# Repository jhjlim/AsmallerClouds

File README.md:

# AsmallerClouds
Schematic/board files for an 8HP version of Clouds

This Eagle project uses the original mutable instruments design files. It simply repositions all components to fit in an 8HP module.
I did this layout as a side project because I love the clouds module and wanted more in my system without sacrificing other space! The only component changes are the crystals to a smaller package, 3mm red/green LEDs and a different illuminated push button. The RESET(SW5) and SYSBOOT(SW4) tactile switches were also dropped and replaced with accesible pads that can be shorted.

Original CAD file, PCB & Schematic and original design elements provided by Mutable Instruments under creative commons CC-BY-SA-3.0 license.

Design contributions are provided by Jason H. J. Lim under Creative Commons CC-BY-SA-3.0 license.

Support of DIY builds is not provided by myself nor Mutable Instruments nor the Mutable Instruments forums, please respect their wishes to not want to answer any questions regarding DIY builds and leave them to continue doing what they do best.

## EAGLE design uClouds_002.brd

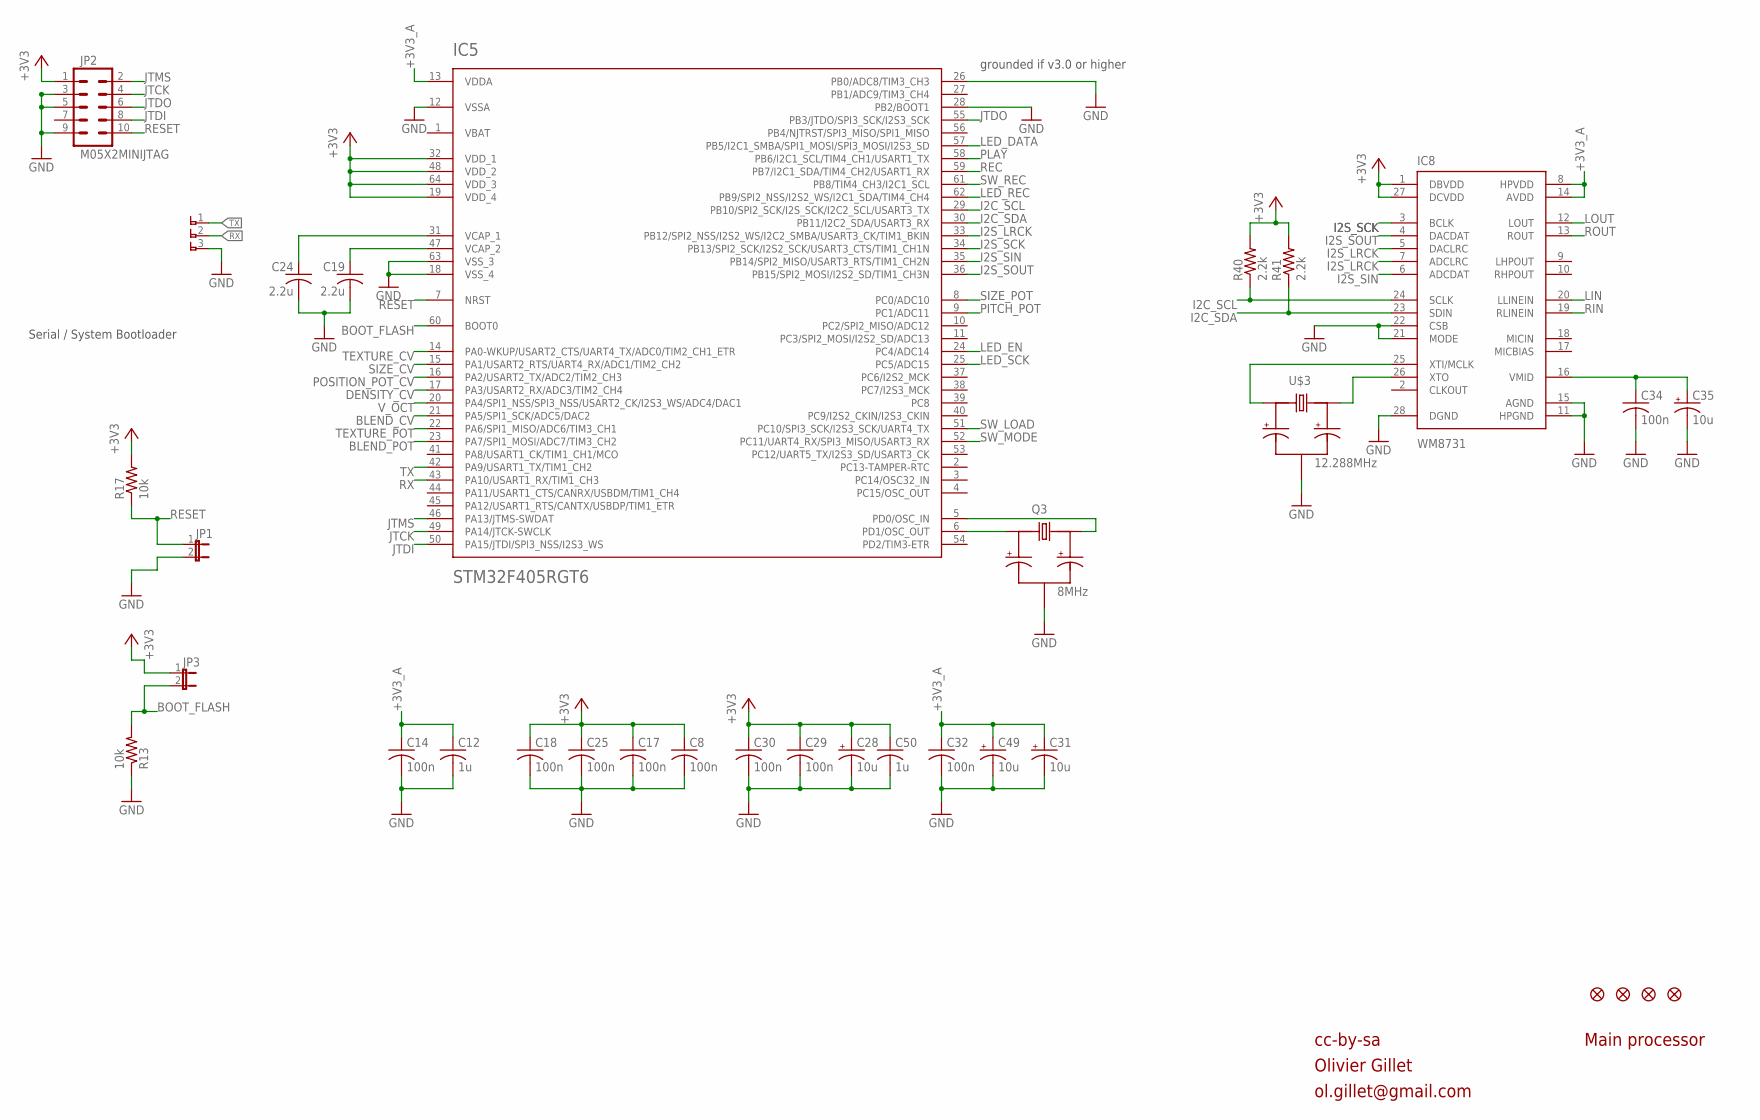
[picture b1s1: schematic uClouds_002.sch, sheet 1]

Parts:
C8, C32, C34: 100n; C0603
C12, C50: 1u; C0603K
C14, C17, C18, C25, C29, C30: 100n; C0603K
C19, C24: 2.2u; C0805K
C28: 10u; 153CLV-0405
C31, C35: 10u; PANASONIC_B
C49: 10u; PANASONIC_A
F1, F2, F3, F4: FIDUCIAL1X2; FIDUCIAL-1X2
IC5: STM32F405RGT6; TQFP-10X10-64
IC8: WM8731; SSOP28
JP1, JP3: JUMPER-2SMD-NO; SJ_2S-NO
JP2: M05X2MINIJTAG; 2X5-1.27
Q3: 8MHz; CRYSTAL_SMALLER
R13, R17: 10k; R0603
R40, R41: 2.2k; R0603
U$3: 12.288MHz; CRYSTAL_SMALLER
U$4: 1X3_SMALL

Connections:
+3V3: C8.1, C17.1, C18.1, C25.1, C28.+, C29.1, C30.1, C50.1, IC5.19 (VDD_4), IC5.32 (VDD_1), IC5.48 (VDD_2), IC5.64 (VDD_3), IC8.1 (DBVDD), IC8.27 (DCVDD), JP2.1, JP3.1, R17.2, R40.2, R41.2; also elsewhere on the board
+3V3_A: C12.1, C14.1, C31.+, C32.1, C49.+, IC5.13 (VDDA), IC8.8 (HPVDD), IC8.14 (AVDD); also elsewhere on the board
BLEND_CV: IC5.21 (PA5/SPI1_SCK/ADC5/DAC2); also elsewhere on the board
BLEND_POT: IC5.23 (PA7/SPI1_MOSI/ADC7/TIM3_CH2); also elsewhere on the board
BOOT_FLASH: IC5.60 (BOOT0), JP3.2, R13.2
DENSITY_CV: IC5.17 (PA3/USART2_RX/ADC3/TIM2_CH4); also elsewhere on the board
GND: C8.2, C12.2, C14.2, C17.2, C18.2, C19.2, C24.2, C25.2, C28.-, C29.2, C30.2, C31.-, C32.2, C34.2, C35.-, C49.-, C50.2, IC5.12 (VSSA), IC5.18 (VSS_4), IC5.26 (PB0/ADC8/TIM3_CH3), IC5.28 (PB2/BOOT1), IC5.63 (VSS_3), IC8.11 (HPGND), IC8.15 (AGND), IC8.21 (MODE), IC8.22 (CSB), IC8.28 (DGND), JP1.2, JP2.3, JP2.5, JP2.9, Q3.GND, R13.1, U$3.GND, U$4.3; also elsewhere on the board
I2C_SCL: IC5.29 (PB10/SPI2_SCK/I2S_SCK/I2C2_SCL/USART3_TX), IC8.24 (SCLK), R40.1
I2C_SDA: IC5.30 (PB11/I2C2_SDA/USART3_RX), IC8.23 (SDIN), R41.1
I2S_LRCK: IC5.33 (PB12/SPI2_NSS/I2S2_WS/I2C2_SMBA/USART3_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), IC8.5 (DACLRC), IC8.7 (ADCLRC)
I2S_SCK: IC5.34 (PB13/SPI2_SCK/I2S2_SCK/USART3_CTS/TIM1_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), IC8.3 (BCLK)
I2S_SIN: IC5.35 (PB14/SPI2_MISO/USART3_RTS/TIM1_CH2N), IC8.6 (ADCDAT)
I2S_SOUT: IC5.36 (PB15/SPI2_MOSI/I2S2_SD/TIM1_CH3N), IC8.4 (DACDAT)
JTCK: IC5.49 (PA14/JTCK-SWCLK), JP2.4
JTDI: IC5.50 (PA15/JTDI/SPI3_NSS/I2S3_WS), JP2.8
JTDO: IC5.55 (PB3/JTDO/SPI3_SCK/I2S3_SCK), JP2.6
JTMS: IC5.46 (PA13/JTMS-SWDAT), JP2.2
LED_DATA: IC5.57 (PB5/I2C1_SMBA/SPI1_MOSI/SPI3_MOSI/I2S3_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); also elsewhere on the board
LED_EN: IC5.24 (PC4/ADC14); also elsewhere on the board
LED_REC: IC5.62 (PB9/SPI2_NSS/I2S2_WS/I2C1_SDA/TIM4_CH4); also elsewhere on the board
LED_SCK: IC5.25 (PC5/ADC15); also elsewhere on the board
LIN: IC8.20 (LLINEIN); also elsewhere on the board
LOUT: IC8.12 (LOUT); also elsewhere on the board
unnamed: IC5.6 (PD1/OSC_OUT), Q3.X1
unnamed: IC8.25 (XTI/MCLK), U$3.X1
unnamed: IC5.5 (PD0/OSC_IN), Q3.X2
unnamed: C19.1, IC5.47 (VCAP_2)
unnamed: C34.1, C35.+, IC8.16 (VMID)
unnamed: C24.1, IC5.31 (VCAP_1)
unnamed: IC8.26 (XTO), U$3.X2
PITCH_POT: IC5.9 (PC1/ADC11); also elsewhere on the board
PLAY: IC5.58 (PB6/I2C1_SCL/TIM4_CH1/USART1_TX); also elsewhere on the board
POSITION_POT_CV: IC5.16 (PA2/USART2_TX/ADC2/TIM2_CH3); also elsewhere on the board
REC: IC5.59 (PB7/I2C1_SDA/TIM4_CH2/USART1_RX); also elsewhere on the board
RESET: IC5.7 (NRST), JP1.1, JP2.10, R17.1
RIN: IC8.19 (RLINEIN); also elsewhere on the board
ROUT: IC8.13 (ROUT); also elsewhere on the board
RX: IC5.43 (PA10/USART1_RX/TIM1_CH3), U$4.2
SIZE_CV: IC5.15 (PA1/USART2_RTS/UART4_RX/ADC1/TIM2_CH2); also elsewhere on the board
SIZE_POT: IC5.8 (PC0/ADC10); also elsewhere on the board
SW_LOAD: IC5.51 (PC10/SPI3_SCK/I2S3_SCK/UART4_TX); also elsewhere on the board
SW_MODE: IC5.52 (PC11/UART4_RX/SPI3_MISO/USART3_RX); also elsewhere on the board
SW_REC: IC5.61 (PB8/TIM4_CH3/I2C1_SCL); also elsewhere on the board
TEXTURE_CV: IC5.14 (PA0-WKUP/USART2_CTS/UART4_TX/ADC0/TIM2_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); also elsewhere on the board
TEXTURE_POT: IC5.22 (PA6/SPI1_MISO/ADC6/TIM3_CH1); also elsewhere on the board
TX: IC5.42 (PA9/USART1_TX/TIM1_CH2), U$4.1
VBAT: IC5.1 (VBAT)
V_OCT: IC5.20 (PA4/SPI1_NSS/SPI3_NSS/USART2_CK/I2S3_WS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); also elsewhere on the board

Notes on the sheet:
cc-by-sa
Olivier Gillet
ol.gillet@gmail.com
Main processor
Serial / System Bootloader
grounded if v3.0 or higher

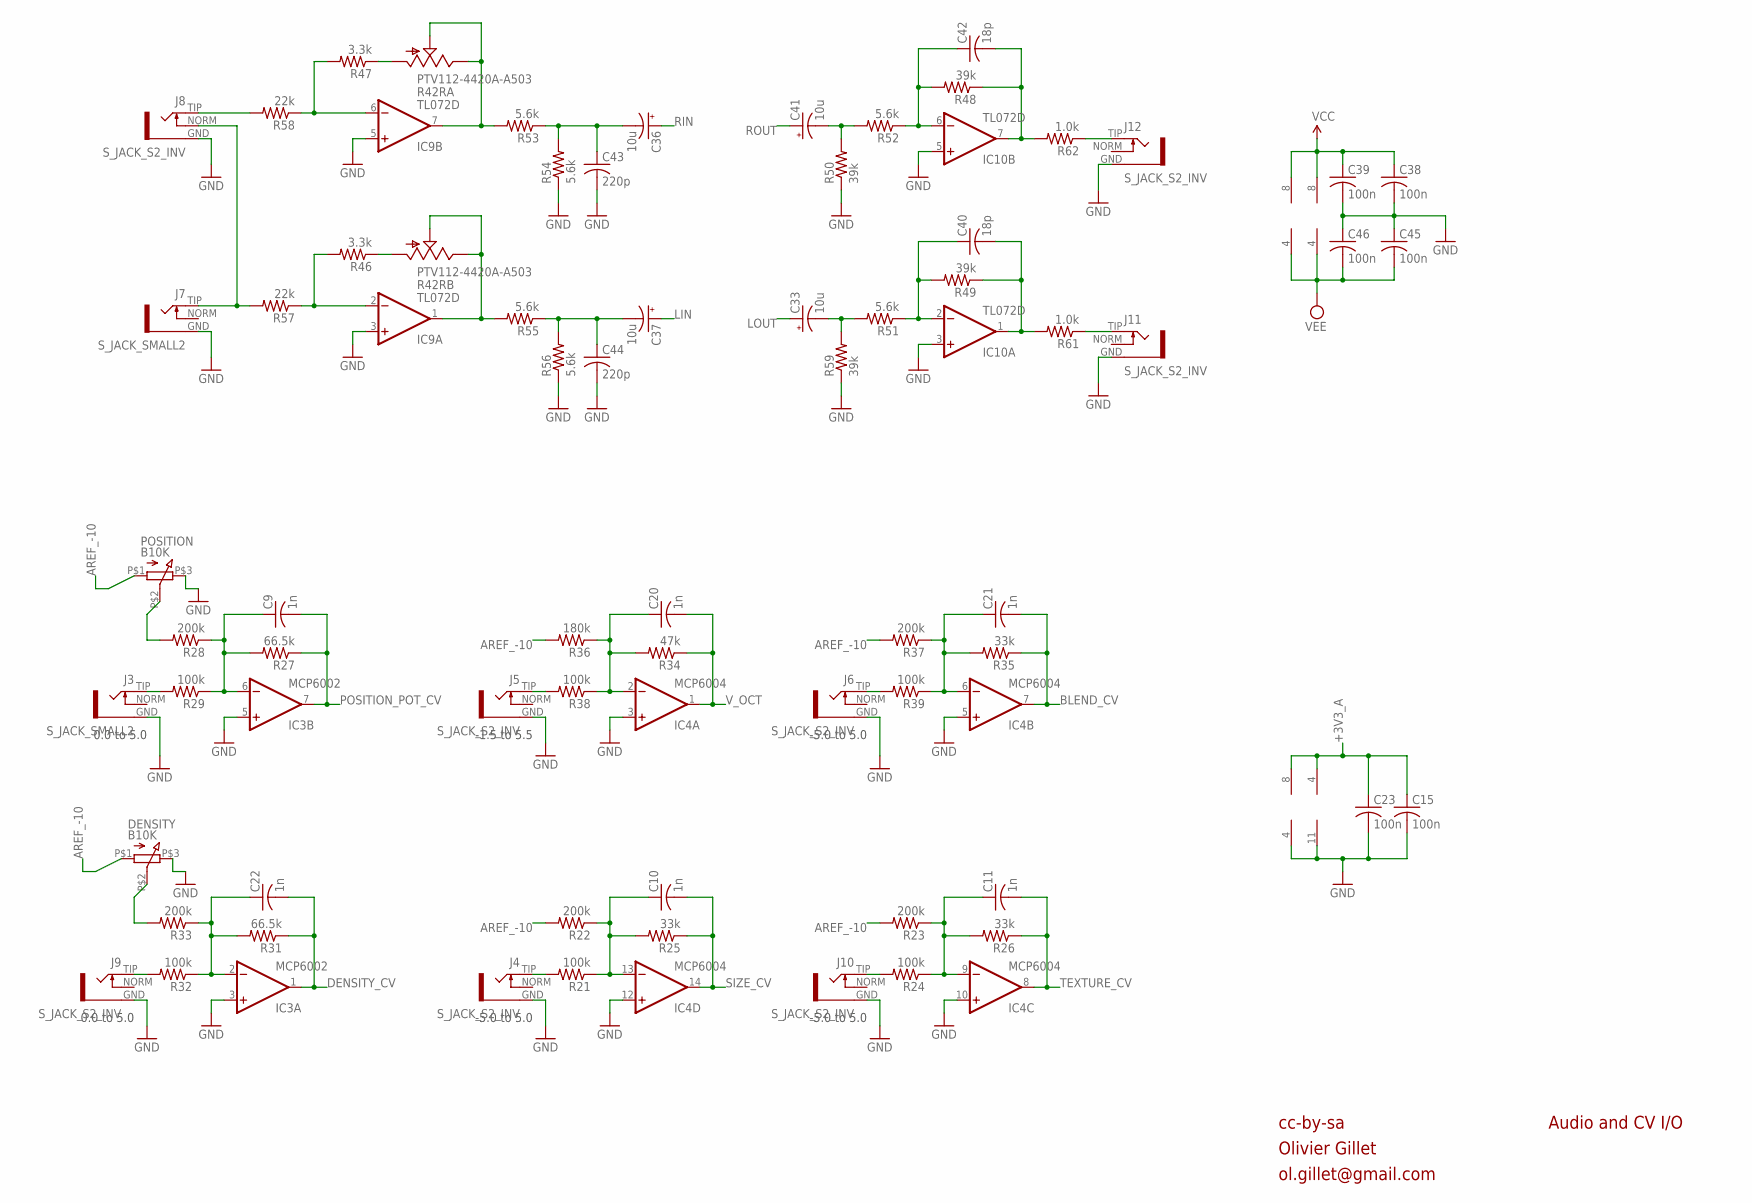
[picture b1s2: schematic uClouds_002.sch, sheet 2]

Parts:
C9, C10, C11, C20, C21, C22: 1n; C0603
C15, C39, C46: 100n; C0603K
C23, C38, C45: 100n; C0603
C33, C36, C37, C41: 10u; PANASONIC_B
C40, C42: 18p; C0603
C43: 220p; C0603K
C44: 220p; C0603
DENSITY: B10K; Q-POT2
IC3: MCP6002; SO08
IC4: MCP6004; SO14
IC9, IC10: TL072D; SO08
J3, J7: S_JACK_SMALL2
J4, J5, J6, J8, J9, J10, J11, J12: S_JACK_S2_INV
POSITION: B10K; Q-POT2
R21, R24, R29, R32, R38, R39: 100k; R0603
R22, R23, R28, R33, R37: 200k; R0603
R25, R26, R35: 33k; R0603
R27, R31: 66.5k; R0603
R34: 47k; R0603
R36: 180k; R0603
R42: PTV112-4420A-A503; BOURNS_PTV112
R46, R47: 3.3k; R0603
R48, R49, R50, R59: 39k; R0603
R51, R52, R53, R54, R55, R56: 5.6k; R0603
R57, R58: 22k; R0603
R61, R62: 1.0k; R0603

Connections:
+3V3_A: C15.1, C23.1, IC3.8 (V+), IC4.4 (V+); also elsewhere on the board
AREF_-10: DENSITY.P$1 (1), POSITION.P$1 (1), R22.2, R23.2, R36.2, R37.2; also elsewhere on the board
BLEND_CV: C21.2, IC4.7 (OUT), R35.1; also elsewhere on the board
DENSITY_CV: C22.2, IC3.1 (OUT), R31.1; also elsewhere on the board
GND: C15.2, C23.2, C38.2, C39.2, C43.2, C44.2, C45.1, C46.1, DENSITY.P$3 (3), IC3.3 (+IN), IC3.4 (V-), IC3.5 (+IN), IC4.3 (+IN), IC4.5 (+IN), IC4.10 (+IN), IC4.11 (V-), IC4.12 (+IN), IC9.3 (+IN), IC9.5 (+IN), IC10.3 (+IN), IC10.5 (+IN), J3.GND, J4.GND, J5.GND, J6.GND, J7.GND, J8.GND, J9.GND, J10.GND, J11.GND, J12.GND, POSITION.P$3 (3), R50.1, R54.1, R56.1, R59.1; also elsewhere on the board
LIN: C37.+; also elsewhere on the board
LOUT: C33.+; also elsewhere on the board
LOUT_JACK: J11.TIP, R61.1
unnamed: J4.TIP, R21.2
unnamed: C10.1, IC4.13 (-IN), R21.1, R22.1, R25.2
unnamed: J10.TIP, R24.2
unnamed: C11.1, IC4.9 (-IN), R23.1, R24.1, R26.2
unnamed: J6.TIP, R39.2
unnamed: J5.TIP, R38.2
unnamed: C20.1, IC4.2 (-IN), R34.2, R36.1, R38.1
unnamed: J9.TIP, R32.2
unnamed: C21.1, IC4.6 (-IN), R35.2, R37.1, R39.1
unnamed: C37.-, C44.1, R55.1, R56.2
unnamed: J8.TIP, R58.2
unnamed: J7.TIP, J8.NORM, R57.2
unnamed: C36.-, C43.1, R53.1, R54.2
unnamed: C41.-, R50.2, R52.2
unnamed: C22.1, IC3.2 (-IN), R31.2, R32.1, R33.1
unnamed: C42.1, IC10.6 (-IN), R48.2, R52.1
unnamed: DENSITY.P$2 (2), R33.2
unnamed: J3.TIP, R29.2
unnamed: C42.2, IC10.7 (OUT), R48.1, R62.2
unnamed: C9.1, IC3.6 (-IN), R27.2, R28.1, R29.1
unnamed: C33.-, R51.2, R59.2
unnamed: C40.1, IC10.2 (-IN), R49.2, R51.1
unnamed: C40.2, IC10.1 (OUT), R49.1, R61.2
unnamed: POSITION.P$2 (2), R28.2
unnamed: IC9.7 (OUT), R42.2P (S), R42.3P (E), R53.2
unnamed: IC9.1 (OUT), R42.2 (S), R42.3 (E), R55.2
unnamed: R42.1P (A), R47.1
unnamed: R42.1 (A), R46.1
unnamed: IC9.6 (-IN), R47.2, R58.1
unnamed: IC9.2 (-IN), R46.2, R57.1
POSITION_POT_CV: C9.2, IC3.7 (OUT), R27.1; also elsewhere on the board
RIN: C36.+; also elsewhere on the board
ROUT: C41.+; also elsewhere on the board
ROUT_JACK: J12.TIP, R62.1
SIZE_CV: C10.2, IC4.14 (OUT), R25.1; also elsewhere on the board
TEXTURE_CV: C11.2, IC4.8 (OUT), R26.1; also elsewhere on the board
VCC: C38.1, C39.1, IC9.8 (V+), IC10.8 (V+); also elsewhere on the board
VEE: C45.2, C46.2, IC9.4 (V-), IC10.4 (V-); also elsewhere on the board
V_OCT: C20.2, IC4.1 (OUT), R34.1; also elsewhere on the board

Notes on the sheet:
cc-by-sa
Olivier Gillet
ol.gillet@gmail.com
Audio and CV I/O
0.0 to 5.0
-1.5 to 5.5
-5.0 to 5.0

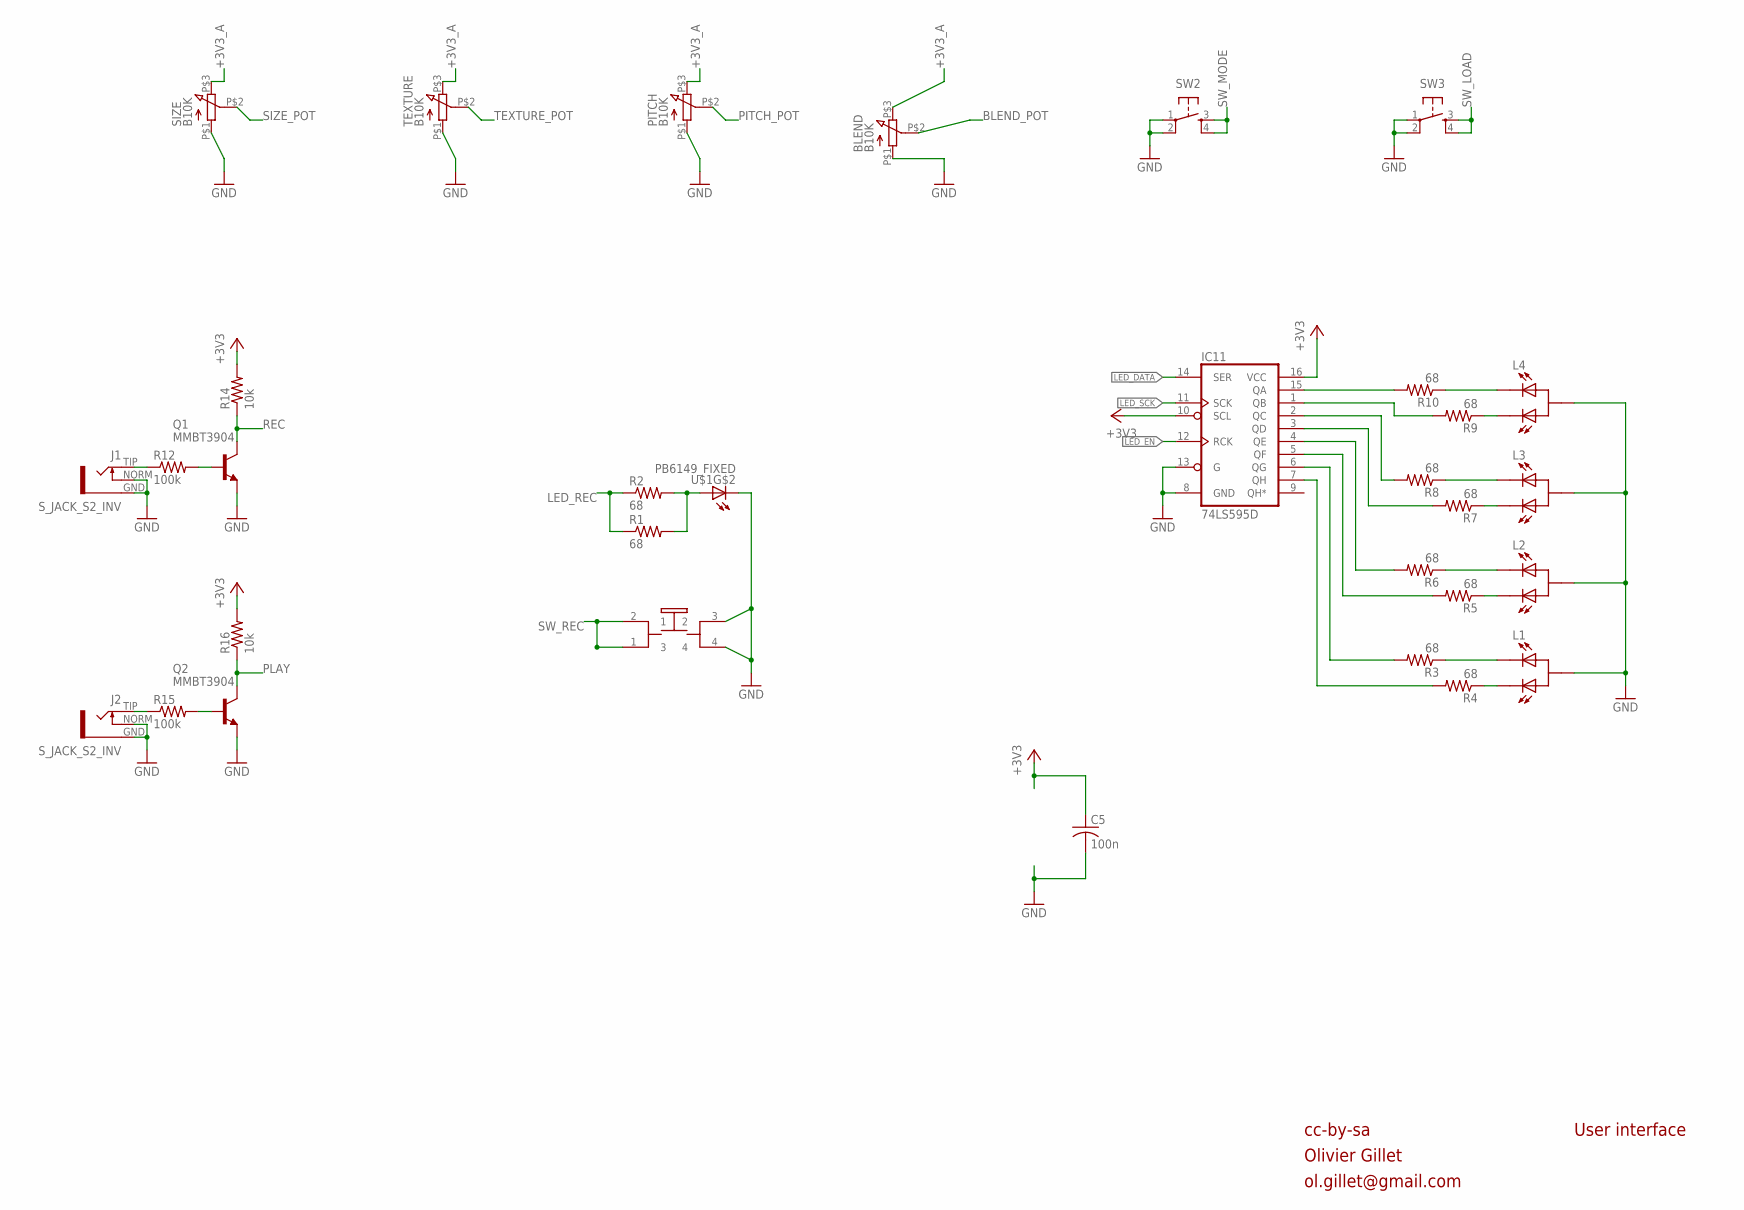
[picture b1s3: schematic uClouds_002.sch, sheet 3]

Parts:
BLEND: B10K; Q-POT2
C5: 100n; C0603
IC11: 74LS595D; SO16
J1, J2: S_JACK_S2_INV
L1, L2, L3, L4: LED_3MM_3PIN
PITCH: B10K; Q-POT2
Q1, Q2: MMBT3904; SOT23-BEC
R1, R2, R3, R4, R5, R6, R7, R8, R9, R10: 68; R0603
R12, R15: 100k; R0603
R14, R16: 10k; R0603
SIZE: B10K; Q-POT2
SW2, SW3: TAC_SWITCHPTH; TACTILE-PTH
TEXTURE: B10K; Q-POT2
U$1: PB6149_FIXED; PB6149L

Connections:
+3V3: C5.1, IC11.10 (SCL), IC11.16 (VCC), R14.2, R16.2; also elsewhere on the board
+3V3_A: BLEND.P$3 (3), PITCH.P$3 (3), SIZE.P$3 (3), TEXTURE.P$3 (3); also elsewhere on the board
BLEND_POT: BLEND.P$2 (2); also elsewhere on the board
GND: BLEND.P$1 (1), C5.2, IC11.8 (GND), IC11.13 (G), J1.GND, J1.NORM, J2.GND, J2.NORM, L1.A, L2.A, L3.A, L4.A, PITCH.P$1 (1), Q1.E, Q2.E, SIZE.P$1 (1), SW2.1, SW2.2, SW3.1, SW3.2, TEXTURE.P$1 (1), U$1.3 (2), U$1.4, U$1.K (C); also elsewhere on the board
LED_DATA: IC11.14 (SER); also elsewhere on the board
LED_EN: IC11.12 (RCK); also elsewhere on the board
LED_REC: R1.1, R2.1; also elsewhere on the board
LED_SCK: IC11.11 (SCK); also elsewhere on the board
unnamed: L4.C1, R9.1
unnamed: L4.C2, R10.1
unnamed: L3.C2, R8.1
unnamed: L3.C1, R7.1
unnamed: L2.C2, R6.1
unnamed: J2.TIP, R15.1
unnamed: Q2.B, R15.2
unnamed: R1.2, R2.2, U$1.A
unnamed: L2.C1, R5.1
unnamed: L1.C2, R3.1
unnamed: L1.C1, R4.1
unnamed: IC11.15 (QA), R10.2
unnamed: IC11.1 (QB), R9.2
unnamed: IC11.2 (QC), R8.2
unnamed: IC11.3 (QD), R7.2
unnamed: IC11.4 (QE), R6.2
unnamed: IC11.5 (QF), R5.2
unnamed: IC11.6 (QG), R3.2
unnamed: IC11.7 (QH), R4.2
unnamed: J1.TIP, R12.1
unnamed: Q1.B, R12.2
PITCH_POT: PITCH.P$2 (2); also elsewhere on the board
PLAY: Q2.C, R16.1; also elsewhere on the board
REC: Q1.C, R14.1; also elsewhere on the board
SIZE_POT: SIZE.P$2 (2); also elsewhere on the board
SW_LOAD: SW3.3, SW3.4; also elsewhere on the board
SW_MODE: SW2.3, SW2.4; also elsewhere on the board
SW_REC: U$1.1 (3), U$1.2 (1); also elsewhere on the board
TEXTURE_POT: TEXTURE.P$2 (2); also elsewhere on the board

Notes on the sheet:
cc-by-sa
Olivier Gillet
ol.gillet@gmail.com
User interface

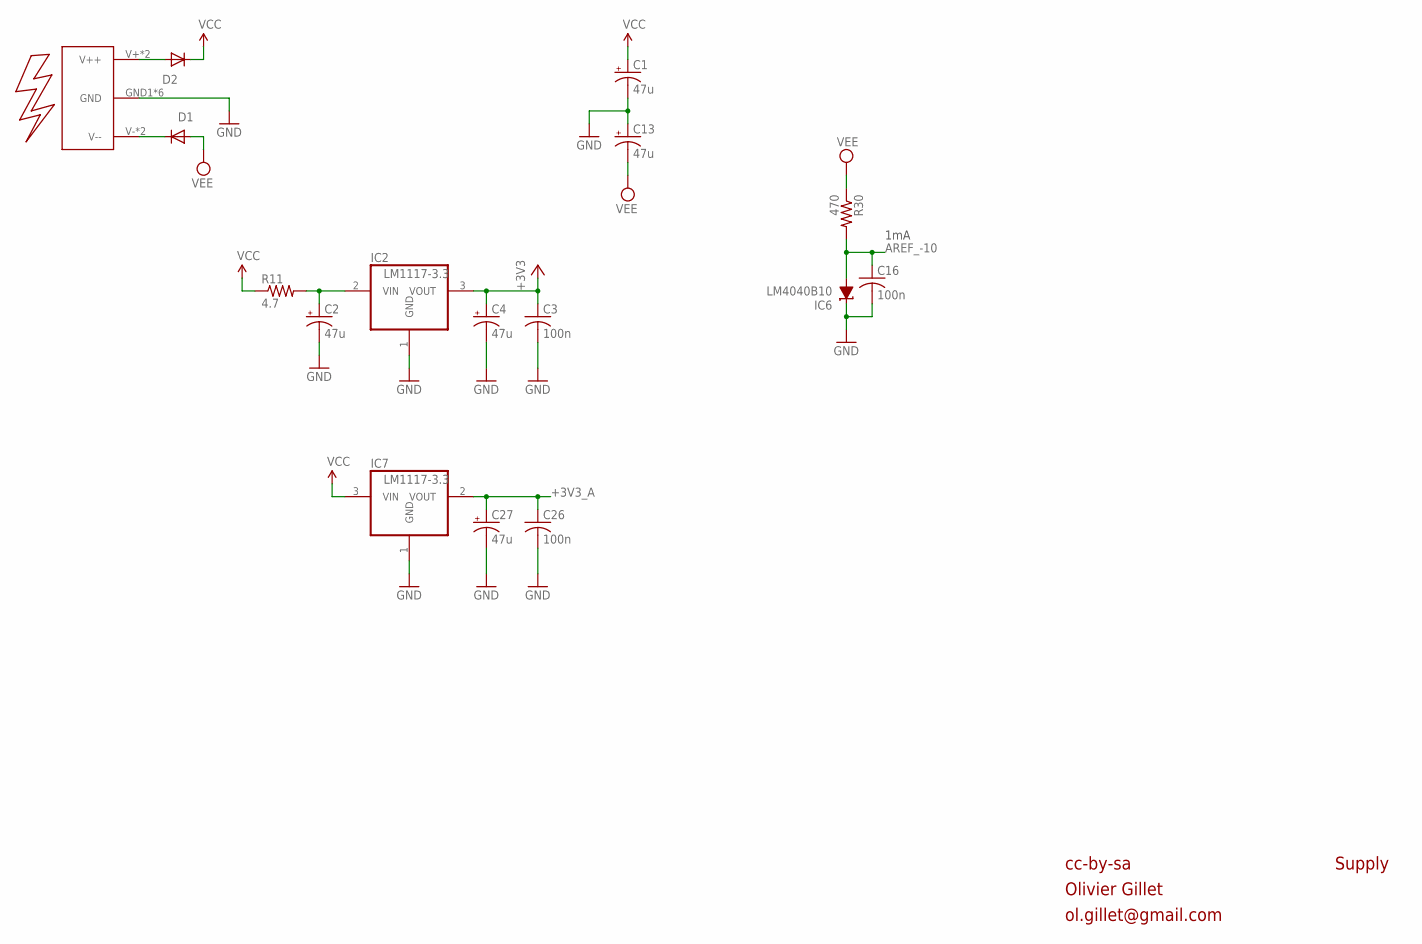
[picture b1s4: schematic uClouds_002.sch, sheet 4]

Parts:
C1, C2, C4, C13, C27: 47u; 153CLV-0505
C3, C16, C26: 100n; C0603
D1, D2: 1N5819HW; SOD123
IC2: LM1117-3.3; TO252
IC6: LM4040B10; DBZ_R-PDSO-G3
IC7: LM1117-3.3; SOT223
R11: 4.7; R1206
R30: 470; R0603
U$2: EURO_POWER2

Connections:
+3V3: C3.1, C4.+, IC2.3 (VOUT); also elsewhere on the board
+3V3_A: C26.1, C27.+, IC7.2 (VOUT); also elsewhere on the board
AREF_-10: C16.1, IC6.2 (A), R30.2; also elsewhere on the board
GND: C1.-, C2.-, C3.2, C4.-, C13.+, C16.2, C26.2, C27.-, IC2.1 (GND), IC6.1 (C), IC7.1 (GND), U$2.GND1 (GND), U$2.GND2 (GND), U$2.GND3 (GND), U$2.GND4 (GND), U$2.GND5 (GND), U$2.GND6 (GND); also elsewhere on the board
unnamed: C2.+, IC2.2 (VIN), R11.2
unnamed: D2.A, U$2.V+ (V++), U$2.V++
unnamed: D1.C, U$2.V- (V--), U$2.V--
VCC: C1.+, D2.C, IC7.3 (VIN), R11.1; also elsewhere on the board
VEE: C13.-, D1.A, R30.1; also elsewhere on the board

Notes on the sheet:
1mA
cc-by-sa
Olivier Gillet
ol.gillet@gmail.com
Supply

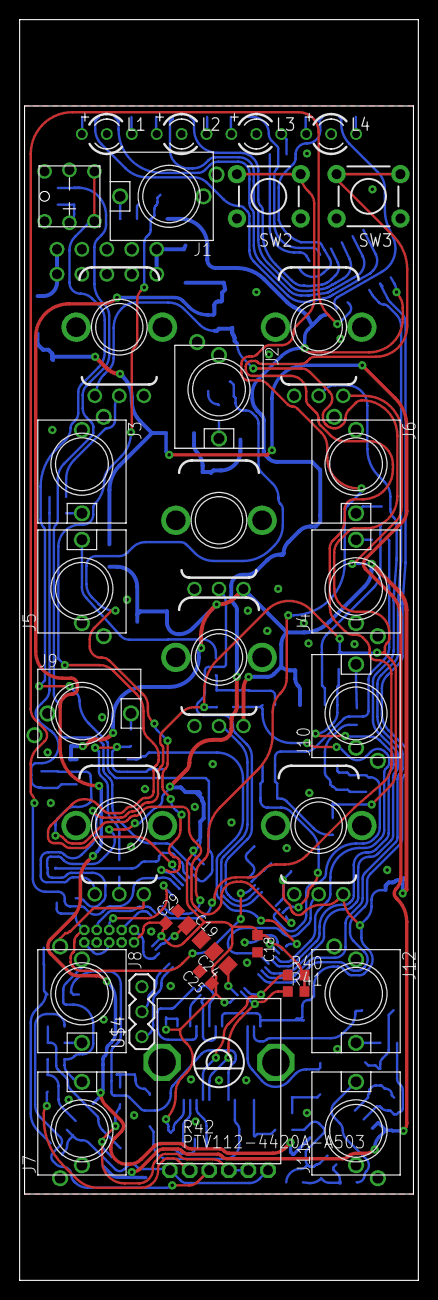
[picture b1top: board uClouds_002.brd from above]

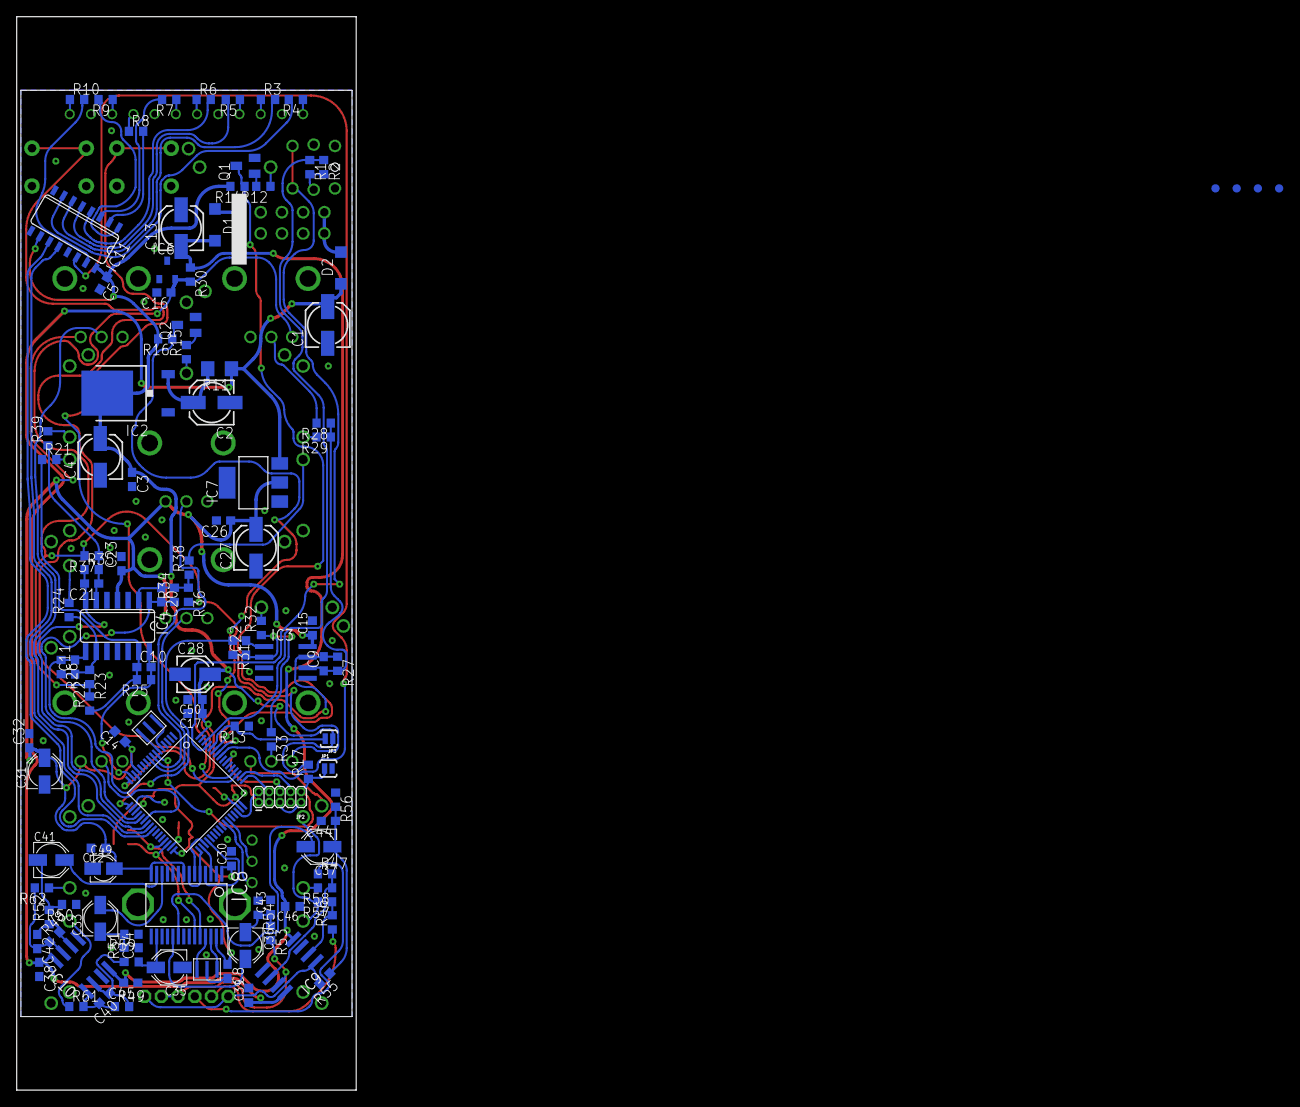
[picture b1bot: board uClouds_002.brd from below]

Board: 2 copper layers, 40.6 x 128.5 mm, 151 parts (116 on the bottom side), 106 nets.

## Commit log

2017-09-22 eagle design files
2018-03-16 component list and map

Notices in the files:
parts and their libraries:
SparkFun-DigitalIC: Licensing: CC v3.0 Share-Alike You are welcome to use this library for commercial purposes.
